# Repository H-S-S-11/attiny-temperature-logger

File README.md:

# ATiny temperature logger

Reads temperature and Real time clock data then writes to an EEPROM over I2C

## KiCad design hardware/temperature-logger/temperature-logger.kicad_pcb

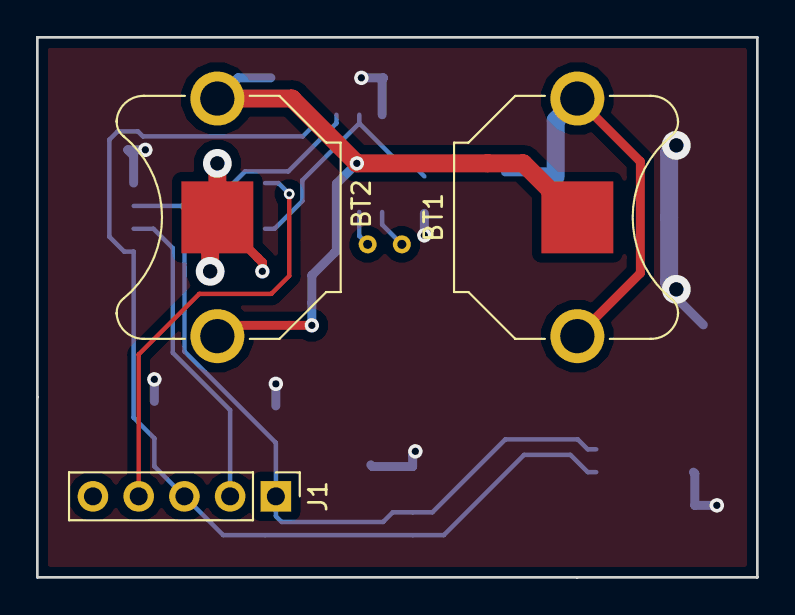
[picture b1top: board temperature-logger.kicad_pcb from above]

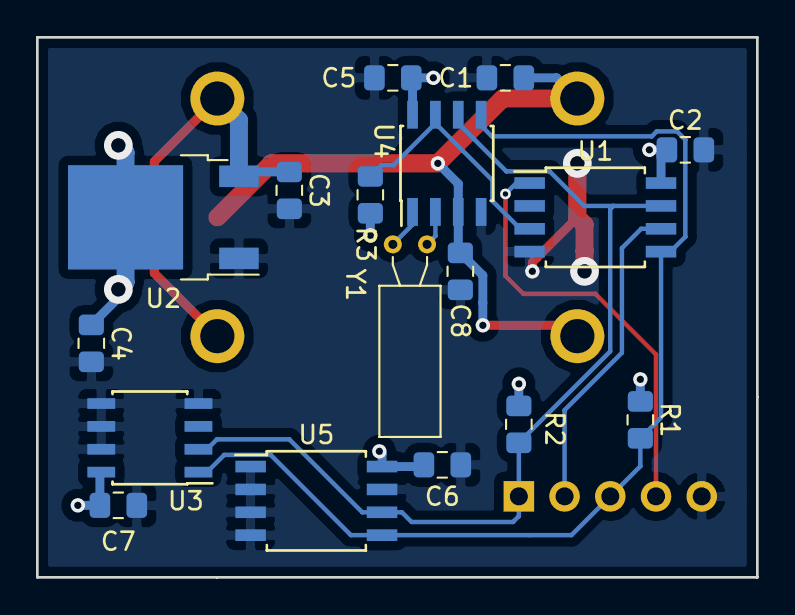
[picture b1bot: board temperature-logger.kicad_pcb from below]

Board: 2 copper layers, 40.0 x 30.0 mm, 20 parts (17 on the bottom side), 11 nets.

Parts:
BT1, BT2: Battery_Cell; BatteryHolder_Keystone_3001_1x12mm
C1, C3, C4: 4.7u; C_0805_2012Metric_Pad1.15x1.40mm_HandSolder
C2, C5, C6, C7, C8: 100n; C_0805_2012Metric_Pad1.15x1.40mm_HandSolder
J1: Conn_01x05; PinHeader_1x05_P2.54mm_Vertical
R1, R2, R3: 10k; R_0805_2012Metric_Pad1.15x1.40mm_HandSolder
U1: ATtiny85-20SU; SOIJ-8_5.3x5.3mm_P1.27mm
U2: NCP1117-5.0_TO252; TO-252-2
U3: MCP9801; SOIC-8_3.9x4.9mm_P1.27mm
U4: DS1307ZN+; SOIC-8_3.9x4.9mm_P1.27mm
U5: 24FC512; SOIJ-8_5.3x5.3mm_P1.27mm
Y1: Crystal; Crystal_C38-LF_D3.0mm_L8.0mm_Horizontal

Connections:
+5V: C2.1, C4.1, C5.1, C6.1, C7.1, R1.1, R2.1, R3.1, U1.8, U2.2, U3.8, U4.8, U5.8
+6V: BT1.1, C3.1, U2.3
+BATT: BT1.2, BT2.1, C1.1, C8.1, U4.3
/MISO: J1.2, U1.6
/SCL: J1.1, R2.2, U1.7, U3.2, U4.6, U5.6
/SDA: J1.3, R1.2, U1.5, U3.1, U4.5, U5.5
/SQW: R3.2, U1.3, U4.7
/~RESET: J1.4, U1.1
GND: BT2.2, C1.2, C2.2, C3.2, C4.2, C5.2, C6.2, C7.2, C8.2, J1.5, U1.4, U2.1, U3.4, U3.5, U3.6, U3.7, U4.4, U5.1, U5.2, U5.3, U5.4, U5.7
unnamed: U4.1, Y1.1
unnamed: U4.2, Y1.2

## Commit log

2019-12-16 Create source files
    Create source files for temperature logger and EEPROM
2019-12-18 i2c first draft
2019-12-18 Set clkpr
    set f_cpu to 500kHz
2019-12-19 i2c test
2019-12-22 Remove i2c source files
    using prewritten libraries (might replace at some point)
2019-12-22 Revert "Remove i2c source files"
    This reverts commit d11664e7f6fee0403072dcaecc1010e4c4db55da.
2019-12-22 Update i2c.c
    Changes the code to actively drive the line high rather than waiting for it to be pulled up
2019-12-22 Removed i2c files for pre written libraries
2019-12-22 i2c libraries
    added i2c libraries from https://github.com/JDat/AtTiny-I2C-master-slave-USI
2019-12-22 Changed main code to use library
    Also added ATtiny85 to library
2019-12-22 Revert "Removed i2c files for pre written libraries"
    This reverts commit 89475dde370c33e3e82814850cd4366902317dd2.
2019-12-22 Revert library changes
2019-12-23 Testing EEPROM writes
2019-12-23 Library download
2019-12-23 Change header file for ATTiny85
2019-12-23 Write test program to write to EEPROM
2019-12-23 Reorganised files
2019-12-23 Added ATMega code
2019-12-23 written functions for 24xx512 using i2c libraries
2020-01-07 Update temperature-log.c
    Start using 24FC512 libraries
2020-02-18 MCP9801 functions
    Reading and writing from the MCP9801 temperature sensor
2020-02-19 include temp sensor in main
    read from temperature sensor, write to EEPROM at an inreasing address
2020-02-19 Read temp sensor
    Testing temp sensor by reading using the ATMega644p
2020-02-19 Temperature recorder
    Code to record temperature every second then read it back from EEPROM
2020-02-19 read from temp sensor
2020-02-20 DS1307 functions
    Wrote function to read data and time from DS1307 RTC
2020-02-20 Add clock reading to main program
    Main program now reads from temperature, then clock, then writes to 8 bytes of EEPROM
2020-02-20 Update main.c
    Change reader to read 8 bytes at once
2020-02-20 Testing reading from DS1307
    Using ATMega to read from RTC and to start the clock/reset seconds counter.
2020-02-20 Problem was hardware
    Need to ensure that the ATTiny is connexted to all devies on the i2c bus
2020-02-20 Fixed reader code so it can read the whole EEPROM
    We have unleashed 100% of its potential
2020-02-20 Fixed clock prescale
    Use enumerated value for clock divider to give the correct clock prescaling, resulting in a 500kHz clock
2020-02-20 Remove blink on PB3
2020-02-21 Setup for long record
    Record at 10s intervals for up to ~20 hours. Dump entire EEPROM contents to csv file (8000 lines with 9 numbers in each: 2 for temperature, 6 for timestamp, 1 for the starting address of that line.
2020-02-21 Changed formatting of readout
    EEPROM readout format changed to be easier to import into excel from .csv
2020-02-21 Update main.c
    Adjusted date time format
2020-05-29 create schematic for PCB
2020-05-29 finish schematic
2020-07-27 pcd redesign to try and minimise signals crossing layers
2020-07-27 finish pcb redesign
2020-09-05 export schematics to pdf
2020-09-06 create gerbers for jlc
2020-09-06 move bat 2 reference
2021-09-15 datasheets and battery holder diagram (add solder)
